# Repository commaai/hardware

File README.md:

# comma hardware

This repo is the home for all comma.ai hardware.

Some of the hardware is fully open source and published here, and the rest is an archive of past hardware sold on the comma shop.

## comma shop

The [comma shop](https://comma.ai/shop) offers our latest hardware for sale.

## Join us!

Want to design and build cool hardware like this?  We're [hiring](https://comma.ai/jobs) hardware engineers and interns; try our [hardware challenge](https://github.com/commaai/harness_tester_challenge).

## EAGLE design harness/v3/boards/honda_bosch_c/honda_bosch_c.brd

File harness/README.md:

# Car harness

## harness connector

The harness serves as the connection to the car. 
In most cars, it is typically connected to the ADAS camera, with only a few exceptions. 
The wiring diagrams for the harnesses we sell are open-sourced and can be found in [here](./v3).

Does your car model lack support from openpilot, and you’re eager to change that? The journey starts with [creating a custom harness](./BUILD_HARNESS.md)!

## harness box

The harness box is like an adapter between the car harness and the comma 3X. 
An integrated relay ensures that you can remove the c3x without your car giving you an error message.
The relay can be controlled by software and opens automatically when openpilot starts.
Internally, the camera's can bus is separated from the rest of the car. 
Some can messages between the camera and the car are simply passed through by software, but messages such as steering commands from the ADAS camera are intercepted and replaced by openpilot.

**The harness box must be connected to the harness, otherwise your car will display error messages.**

## obd-c

The [OBD-C Cable](https://comma.ai/shop/obd-c-cable) is a USB-C cable where all internal lines are fully connected, complying with the USB-C 3.1 Gen 2 or USB-C 3.2 Gen 2 specifications. 
The OBD-C pinout is specifed [here](./OBD-C.sch.pdf).
You might ask why are there short and long cables in the store? The long cable is typically used when the car harness is not connected at the adas camera near the comma 3X. 

All the exceptions are listed here on this [page]("https://www.comma.ai/shop/car-harness")

**NOTE: bad cables are common source of errors. To avoid unnecessary frustration, we recommend purchasing a [high-quality cable](https://comma.ai/shop/obd-c-cable) that meets the specifications.**

## comma power

comma power is an optional, yet recommended, addition to enhance your device's capabilities. 
The four-pin connection provides both power and OBD CAN connectivity.

While you can operate the device without comma power, it will only be powered while driving.
**With comma power** the device remains continuously powered, unlocking more features like a dashcam, remote tracking, SSH access, and more.

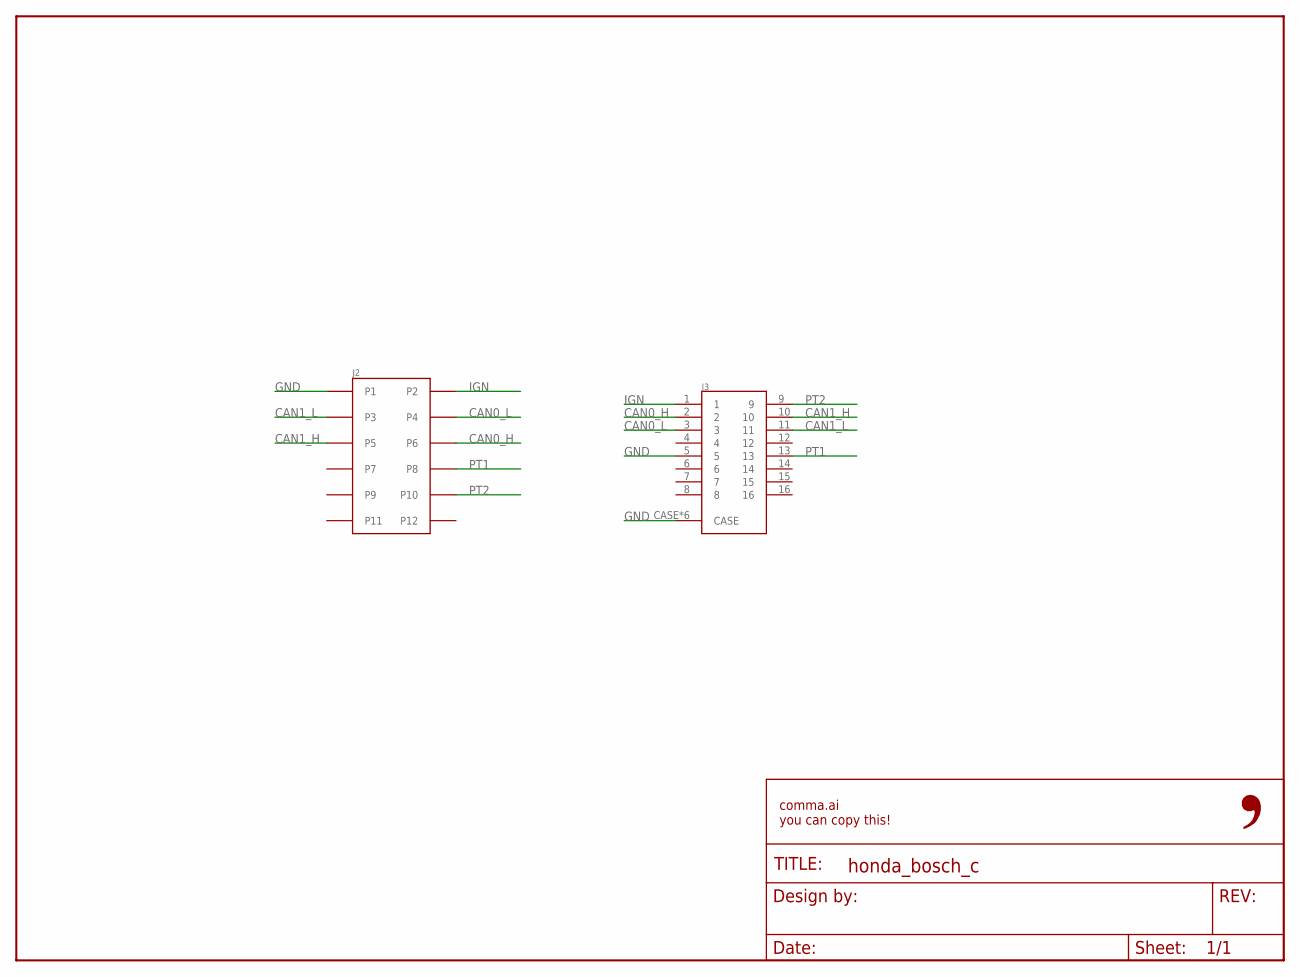
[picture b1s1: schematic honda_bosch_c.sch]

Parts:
FRAME1: FRAME-LETTER-OPENNO_PACKAGE; DUMMY
J2: 5018761240
J3: GT25H2-16DP-2.2H

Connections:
CAN0_H: J2.P6, J3.2
CAN0_L: J2.P4, J3.3
CAN1_H: J2.P5, J3.10
CAN1_L: J2.P3, J3.11
GND: J2.P1, J3.5, J3.CASE, J3.CASE2 (CASE), J3.CASE3 (CASE), J3.CASE4 (CASE), J3.CASE5 (CASE), J3.CASE6 (CASE)
IGN: J2.P2, J3.1
PT1: J2.P8, J3.13
PT2: J2.P10, J3.9

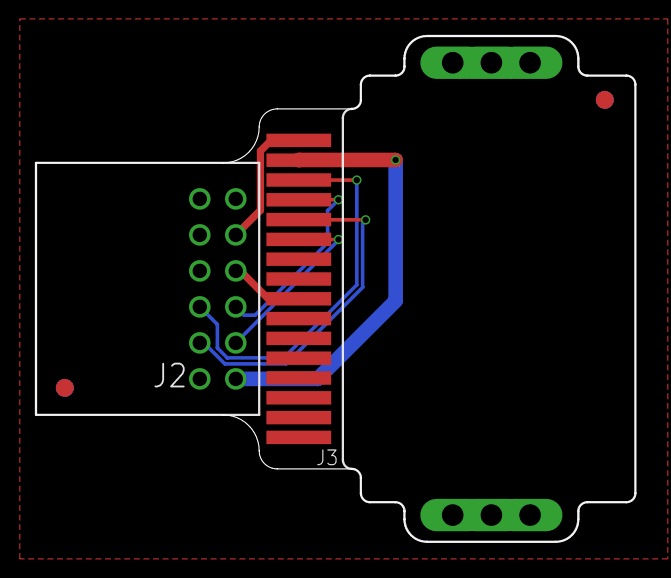
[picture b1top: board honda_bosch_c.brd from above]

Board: 2 copper layers, 33.3 x 28.1 mm, 6 parts (1 on the bottom side), 8 nets.

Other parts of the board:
E$1: LOGO
U$1, U$3: FIDUCIAL

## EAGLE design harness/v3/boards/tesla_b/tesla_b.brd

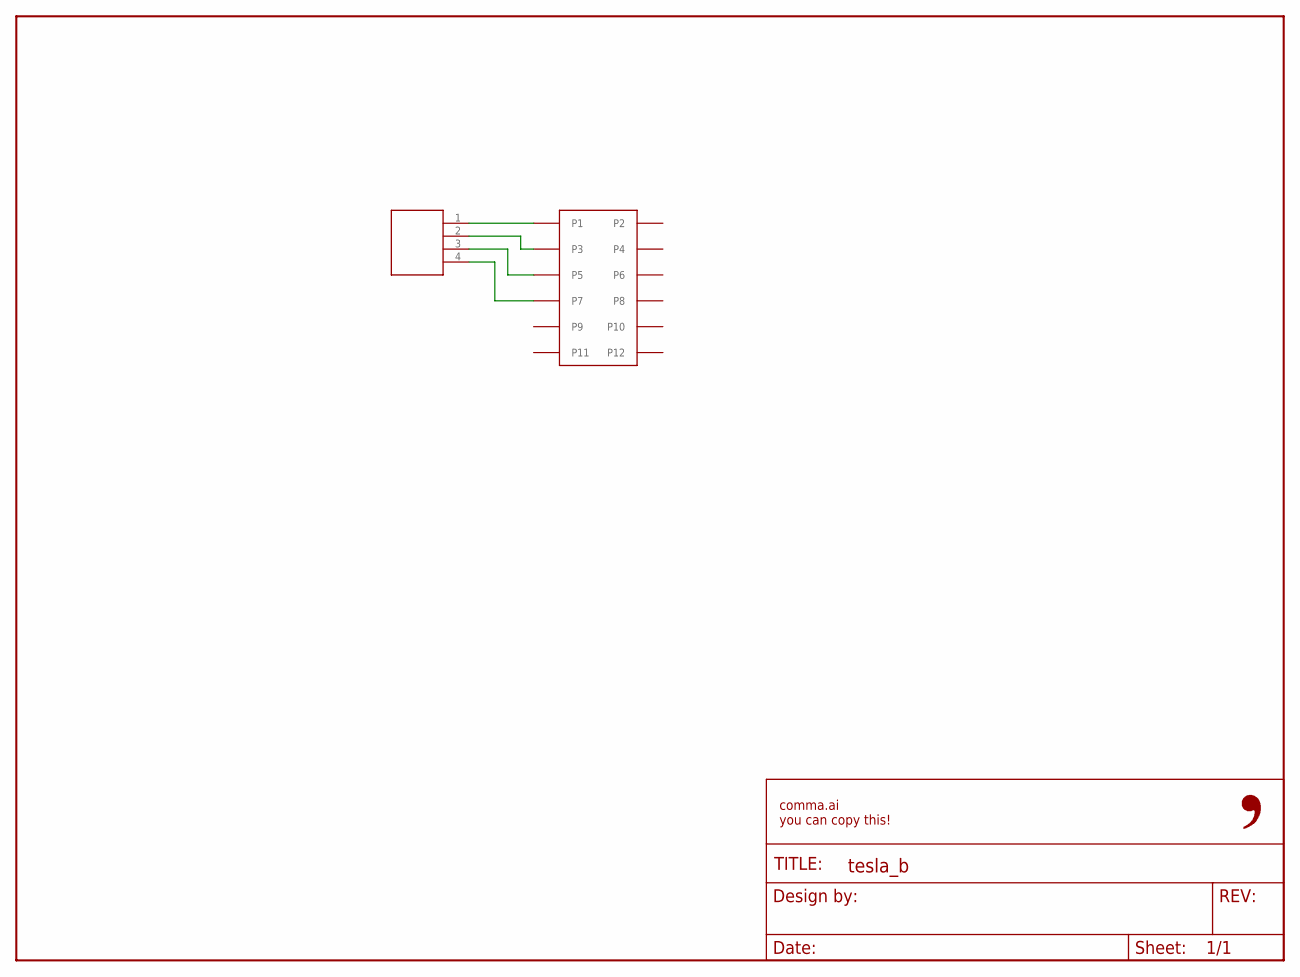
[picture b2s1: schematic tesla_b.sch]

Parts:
FRAME1: FRAME-LETTER-OPENNO_PACKAGE; DUMMY
J1: 5016451220
J2: M04-641211-4; 641211-4

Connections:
unnamed: J1.P1, J2.1
unnamed: J1.P3, J2.2
unnamed: J1.P5, J2.3
unnamed: J1.P7, J2.4

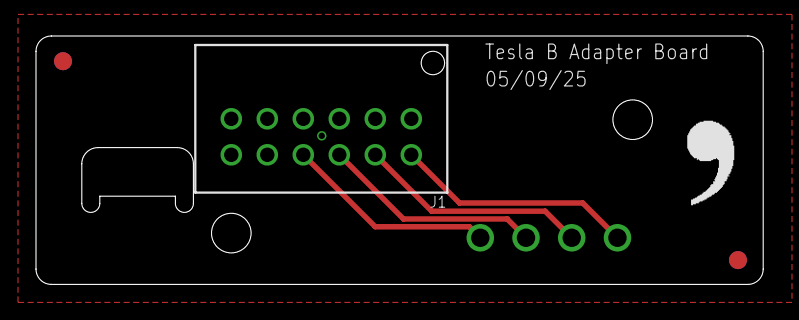
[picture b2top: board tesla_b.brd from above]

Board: 2 copper layers, 40.4 x 13.8 mm, 6 parts (1 on the bottom side), 4 nets.

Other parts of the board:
U$1, U$2: FIDUCIAL
U$3: LOGO

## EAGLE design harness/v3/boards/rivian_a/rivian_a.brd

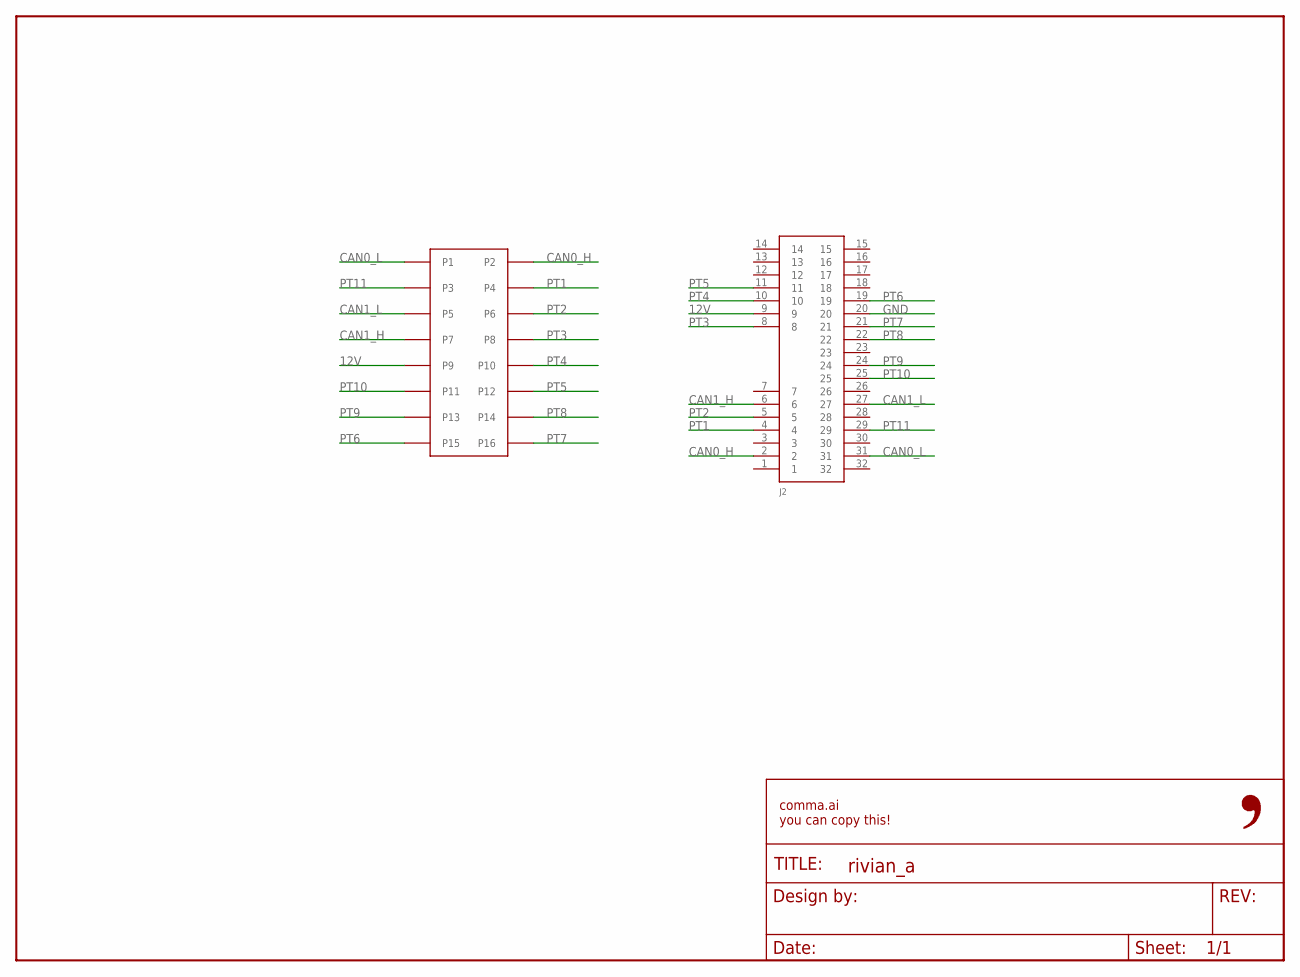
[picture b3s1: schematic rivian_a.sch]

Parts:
FRAME1: FRAME-LETTER-OPENNO_PACKAGE; DUMMY
J1: 5018761640
J2: 2177419-3

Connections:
12V: J1.P9, J2.9
CAN0_H: J1.P2, J2.2
CAN0_L: J1.P1, J2.31
CAN1_H: J1.P7, J2.6
CAN1_L: J1.P5, J2.27
GND: J2.20
PT1: J1.P4, J2.4
PT2: J1.P6, J2.5
PT3: J1.P8, J2.8
PT4: J1.P10, J2.10
PT5: J1.P12, J2.11
PT6: J1.P15, J2.19
PT7: J1.P16, J2.21
PT8: J1.P14, J2.22
PT9: J1.P13, J2.24
PT10: J1.P11, J2.25
PT11: J1.P3, J2.29

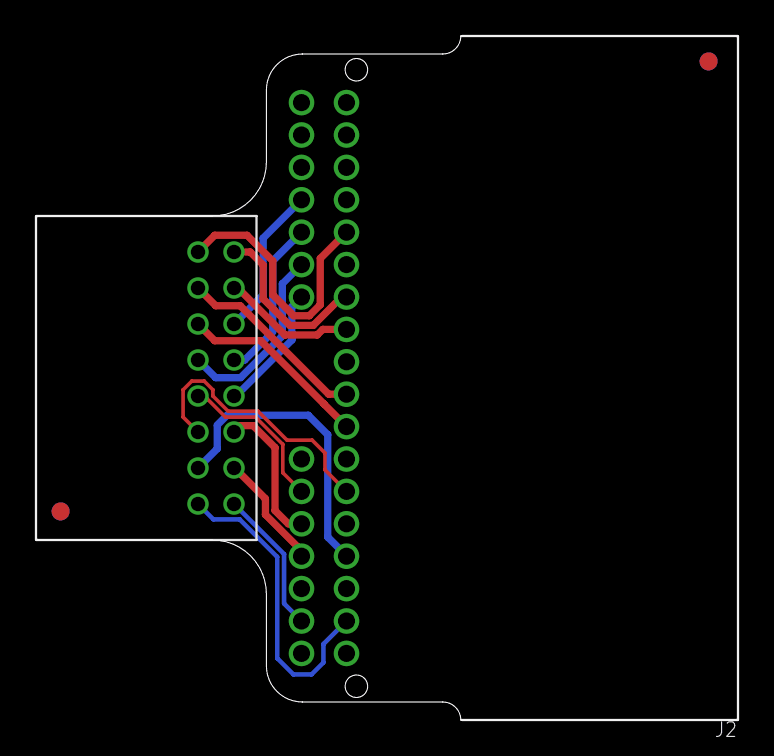
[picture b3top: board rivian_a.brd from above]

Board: 2 copper layers, 39.0 x 38.0 mm, 6 parts (1 on the bottom side), 16 nets.

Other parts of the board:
U$1: LOGO
U$2, U$3: FIDUCIAL

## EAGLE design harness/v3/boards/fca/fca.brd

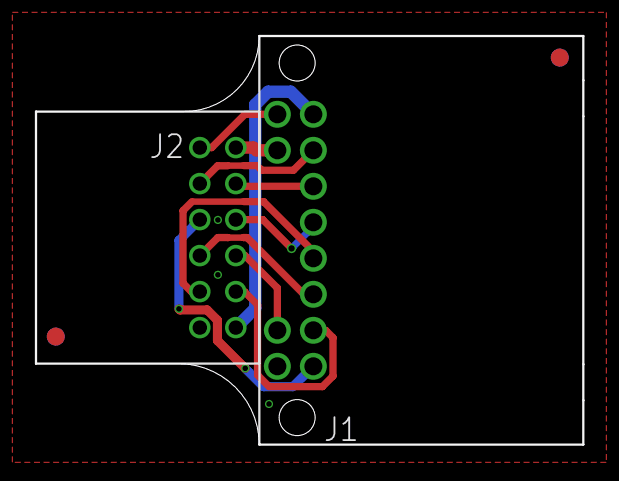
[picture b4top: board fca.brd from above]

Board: 2 copper layers, 30.4 x 22.7 mm, 6 parts (1 on the bottom side), 12 nets.

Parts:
FRAME1: FRAME-LETTER-OPENNO_PACKAGE; DUMMY
J1: 0348260124
J2: 5018761240
U$1: LOGO
U$2, U$3: FIDUCIAL

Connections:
CAN0_H: J1.P2, J2.P6
CAN0_L: J1.P6, J2.P4
CAN1_H: J1.P7, J2.P5
CAN1_L: J1.P8, J2.P3
GND: J1.P1, J2.P1
IGN: J1.P12, J2.P2
PT1: J1.P9, J2.P8
PT2: J1.P10, J2.P10
PT3: J1.P3, J2.P12
PT4: J1.P5, J2.P7
PT5: J1.P11, J2.P9
PT6: J1.P4, J2.P11

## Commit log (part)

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2025-02-17 fix image links
2025-02-17 Fix broken image links (#3)
2025-03-07 add power extender
2025-03-07 update harness schematics
2025-03-24 update harness images
2025-04-08 add rivian and tesla A
2025-04-08 update harness images (#5)
2025-05-04 comma zero
2025-05-14 Update README.md (#8)
2025-06-25 Note late c3s have different sensors
    Closes #2
2025-06-25 Apply suggestions from code review
2025-06-25 Note late c3s have different sensors (#9)
    * Note late c3s have different sensors
    Closes #2
    * Apply suggestions from code review
    * Update README.md
    ---------
2025-06-28 comma zero (#7)
    * comma zero
    * Update README.md
    ---------
2025-08-27 comma three flashing instructions
2025-08-29 flash
2025-08-30 feat: add last openpilot version to comma 3
2025-09-01 feat: add last openpilot version to comma 3 (#13)
2025-11-09 add tesla b
2025-11-09 comma four
2025-11-09 fix url
2025-11-10 shop links
2025-11-10 body
2026-01-26 add debug connector pinout
2026-04-10 add c4 hat/stand
2026-04-13 bosch c pcba
2026-04-15 Rename C4_stand.3mf to comma_four_stand.3mf
2026-04-15 body: add comma four hat (#21)
    * add comma 4 hat 3D file for body v1
2026-04-16 Added BYD-f harness from Gutek. BYD bounty that MLP claims
